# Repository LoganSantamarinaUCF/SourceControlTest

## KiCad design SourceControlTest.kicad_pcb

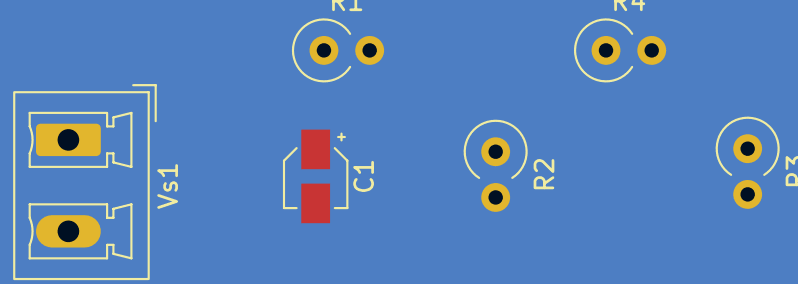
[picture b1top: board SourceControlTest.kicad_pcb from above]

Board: 2 copper layers, 6 parts (0 on the bottom side), 4 nets.

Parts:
C1: 10uF; CP_Elec_3x5.3
R1: 20k; R_Axial_DIN0309_L9.0mm_D3.2mm_P2.54mm_Vertical
R2: 10k; R_Axial_DIN0309_L9.0mm_D3.2mm_P2.54mm_Vertical
R3, R4: R_US; R_Axial_DIN0309_L9.0mm_D3.2mm_P2.54mm_Vertical
Vs1: 10v; PhoenixContact_MCV_1,5_2-G-5.08_1x02_P5.08mm_Vertical

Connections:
/SecondDivider/Division_In: R1.2, R2.1, R4.1
/SecondDivider/Voltage_Output: R3.1, R4.2
GND: C1.2, R2.2, R3.2, Vs1.2 (-)
unnamed: C1.1, R1.1, Vs1.1 (+)
